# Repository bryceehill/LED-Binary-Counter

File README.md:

#Introduction

The Montana Tech Binary Counter is a project created by the Electrical Engineering Department.  All files to recreate it are available here.  Potential students can request a binary counter through this link:
https://www.mtech.edu/electrical-engineering/circuit-handout/index.html

To get started plug the binary counter into a computer via a USB cable.  In windows download putty.exe, find the port associated with the counter using "Device Manager" and open that serial port.
Getting started may need some direction.  Watch this video:
https://youtu.be/mpABhzl5tEQ

The current version of the binary counter is the ARM processor version.  You can find all connected files, firmware, designs within this repository.

# LED-Binary-Counter
Public Files for the LED Binary Counter.  Modify, Code, Change, on your own.

There are two versions.  The original one had a MSP430 G2553 as it's controller.  The new version uses an ATSAMD21E15B with added usb utility
Both chips have 10 LEDs that they control.

ARM - ATSAMD21E15B Documentation---------------------------------------------------------------------------

Pinout
PA00 - LED 0
PA01 - LED 1
PA02 - LED 2
PA03 - LED 3
PA04 - LED 4
PA05 - LED 5
PA06 - LED 6
PA07 - LED 7
PA08 - LED 8
PA09 - LED 9
PA16 - PushButton

MSP430 Documentation---------------------------------------------------------------------------------

This respository contains all of the files used to create the Montana Tech LED Bar Graph Counter
The bar graph counter is a piece of SWAG intended for potential students.
There are 10 LEDs controlled by an MSP430 G2553 Microcontroller (TI Look it up)

A PCB was created for use with the QFN-32 package of the G2553
Code was created using code composer studio in C programming language. All files are available
More instructions can be found for new users via the web page:
https://www.mtech.edu/electrical-engineering/circuit-handout/

Potential students can request a free complete system
Pinout of the MSP430 are the following
* 1.0 -
 * 1.1 - RX0  UART Receive
 * 1.2 - TX0  UART Transmit
 * 1.3 - SW1  Pushbutton
 * 1.4 -
 * 1.5 -
 * 1.6 -
 * 1.7 -
 * 2.0 - L8  LED 8
 * 2.1 - L9  LED 9
 * 2.2 -
 * 2.3 -
 * 2.4 -
 * 2.5 -
 * 2.6 -
 * 2.7 -
 * 3.0 - L0  LED 0
 * 3.1 - L1  LED 1
 * 3.2 - L2  LED 2
 * 3.3 - L3  LED 3
 * 3.4 - L4  LED 4
 * 3.5 - L5  LED 5
 * 3.6 - L6  LED 6
 * 3.7 - L7  LED 7

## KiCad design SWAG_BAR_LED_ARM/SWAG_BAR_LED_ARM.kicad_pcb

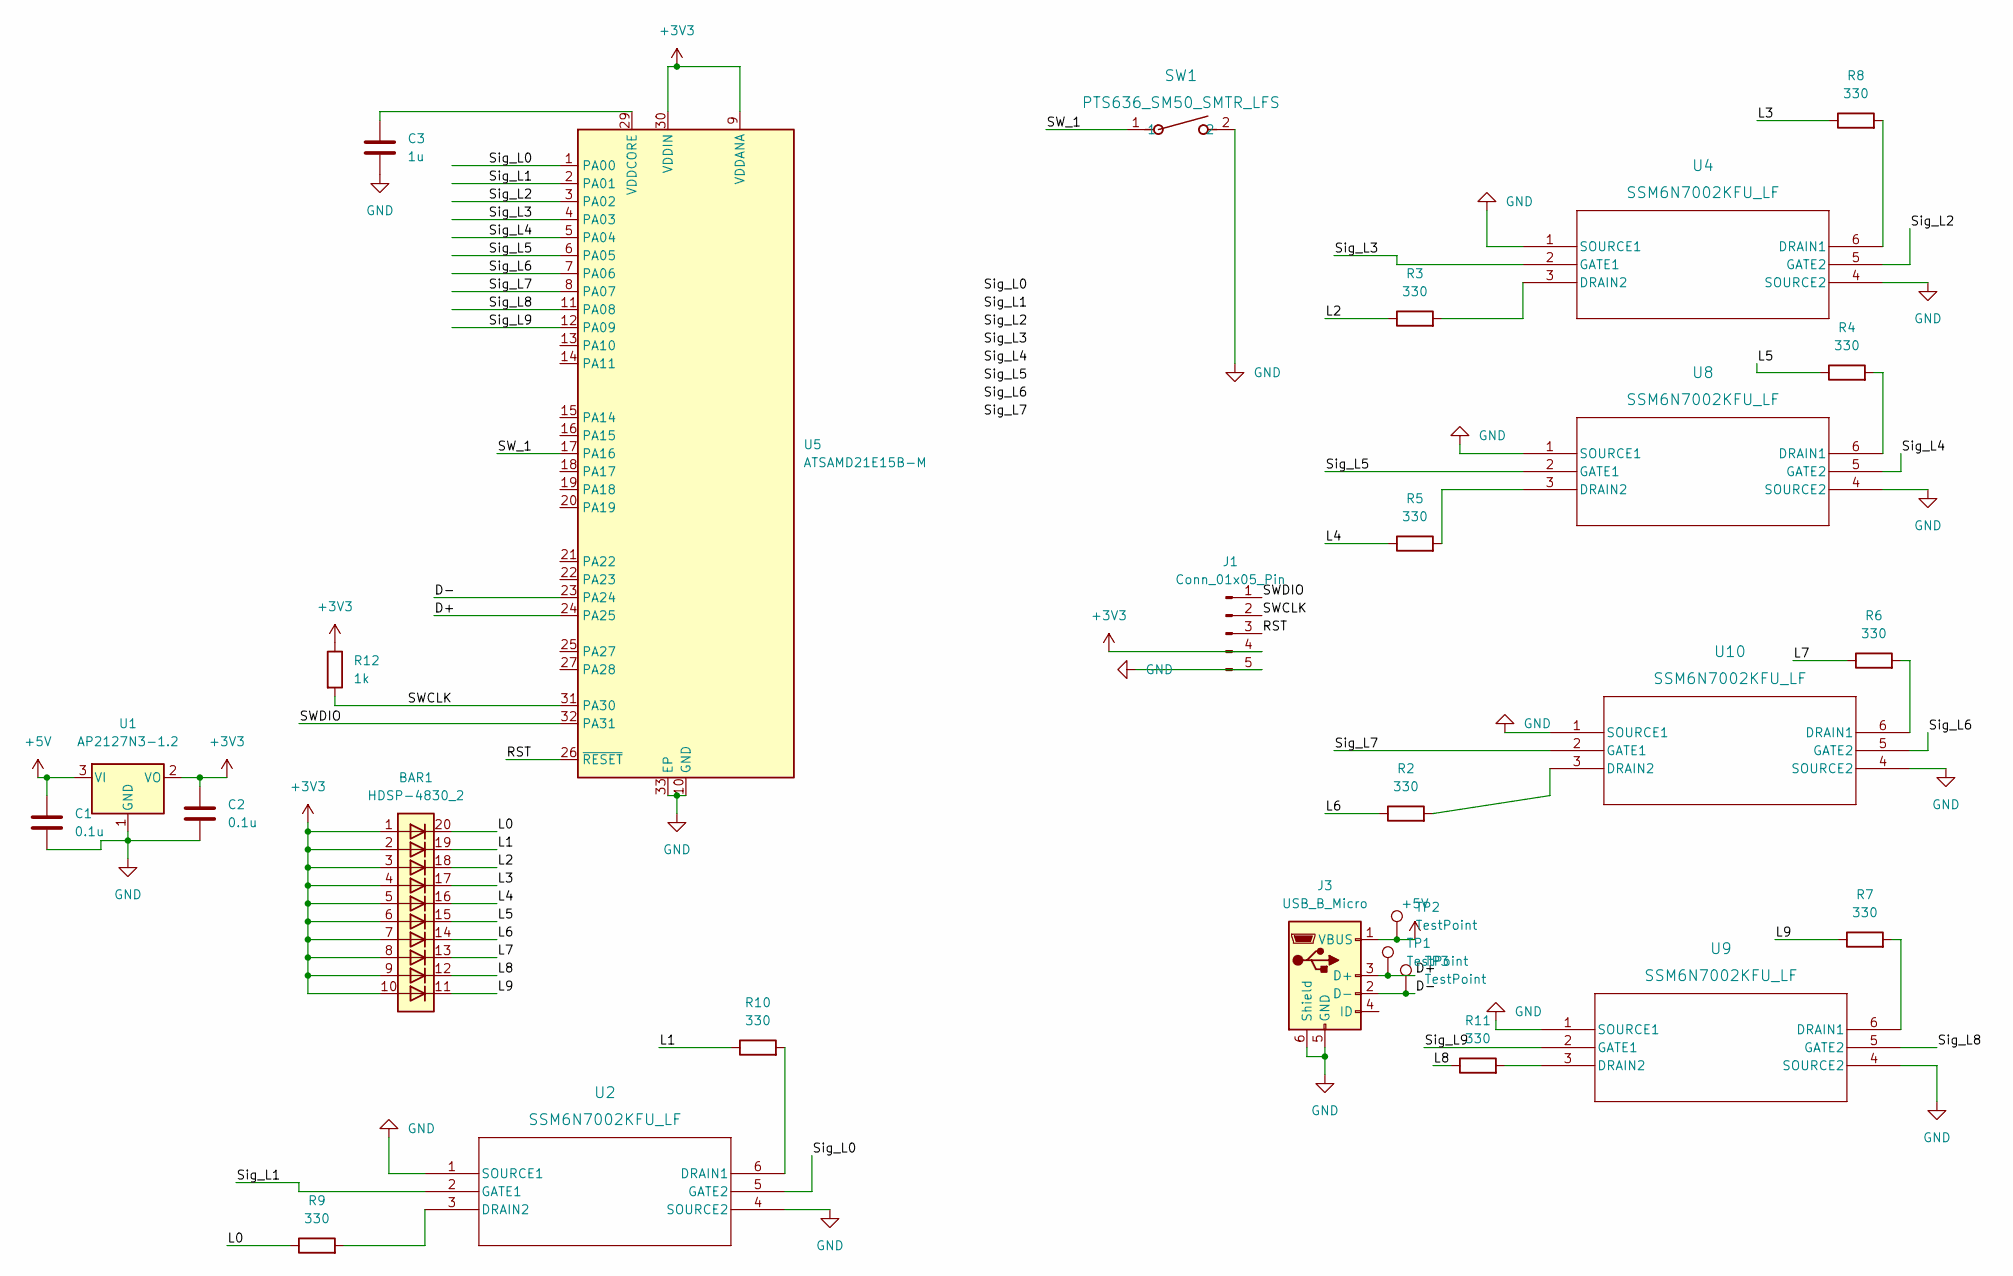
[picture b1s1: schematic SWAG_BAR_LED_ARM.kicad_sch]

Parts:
BAR1: HDSP-4830_2; HDSP-4830
C1, C2: 0.1u; C_0603_1608Metric
C3: 1u; C_0603_1608Metric
J1: Conn_01x05_Pin; PinHeader_1x05_P2.54mm_Vertical
J3: USB_B_Micro; USB_Micro-B_Wuerth_629105150521
R2, R3, R4, R5, R6, R7, R8, R9, R10, R11: 330; R_0603_1608Metric
R12: 1k; R_0603_1608Metric
SW1: PTS636_SM50_SMTR_LFS; SW_PTS636_SMT-G_5_CNK
TP1, TP2, TP3: TestPoint; TestPoint_Loop_D2.50mm_Drill1.0mm_LowProfile
U1: AP2127N3-1.2; TSOT-23
U2, U4, U8, U9, U10: SSM6N7002KFU_LF; SOT-363 US6_TOS
U5: ATSAMD21E15B-M; QFN-32-1EP_5x5mm_P0.5mm_EP3.6x3.6mm

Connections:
+3V3: BAR1.1 (A), BAR1.2 (A), BAR1.3 (A), BAR1.4 (A), BAR1.5 (A), BAR1.6 (A), BAR1.7 (A), BAR1.8 (A), BAR1.9 (A), BAR1.10 (A), C2.1, J1.4, R12.1, U1.2 (VO), U5.9 (VDDANA), U5.30 (VDDIN)
+5V: C1.1, J3.1 (VBUS), TP2.1, U1.3 (VI)
/D+: J3.3 (D+), TP1.1, U5.24 (PA25)
/D-: J3.2 (D-), TP3.1, U5.23 (PA24)
/L0: BAR1.20 (K), R9.1
/L1: BAR1.19 (K), R10.1
/L2: BAR1.18 (K), R3.1
/L3: BAR1.17 (K), R8.1
/L4: BAR1.16 (K), R5.1
/L5: BAR1.15 (K), R4.1
/L6: BAR1.14 (K), R2.1
/L7: BAR1.13 (K), R6.1
/L8: BAR1.12 (K), R11.1
/L9: BAR1.11 (K), R7.1
/RST: J1.3, U5.26 (~RESET)
/SWCLK: J1.2, R12.2, U5.31 (PA30)
/SWDIO: J1.1, U5.32 (PA31)
/SW_1: SW1.1, U5.17 (PA16)
/Sig_L0: U2.5 (GATE2), U5.1 (PA00)
/Sig_L1: U2.2 (GATE1), U5.2 (PA01)
/Sig_L2: U4.5 (GATE2), U5.3 (PA02)
/Sig_L3: U4.2 (GATE1), U5.4 (PA03)
/Sig_L4: U5.5 (PA04), U8.5 (GATE2)
/Sig_L5: U5.6 (PA05), U8.2 (GATE1)
/Sig_L6: U5.7 (PA06), U10.5 (GATE2)
/Sig_L7: U5.8 (PA07), U10.2 (GATE1)
/Sig_L8: U5.11 (PA08), U9.5 (GATE2)
/Sig_L9: U5.12 (PA09), U9.2 (GATE1)
GND: C1.2, C2.2, C3.2, J1.5, J3.5 (GND), J3.6 (Shield), SW1.2, U1.1 (GND), U2.1 (SOURCE1), U2.4 (SOURCE2), U4.1 (SOURCE1), U4.4 (SOURCE2), U5.10 (GND), U5.28 (GND), U5.33 (EP), U8.1 (SOURCE1), U8.4 (SOURCE2), U9.1 (SOURCE1), U9.4 (SOURCE2), U10.1 (SOURCE1), U10.4 (SOURCE2)
unnamed: R10.2, U2.6 (DRAIN1)
unnamed: R9.2, U2.3 (DRAIN2)
unnamed: R8.2, U4.6 (DRAIN1)
unnamed: R3.2, U4.3 (DRAIN2)
unnamed: C3.1, U5.29 (VDDCORE)
unnamed: R4.2, U8.6 (DRAIN1)
unnamed: R5.2, U8.3 (DRAIN2)
unnamed: R7.2, U9.6 (DRAIN1)
unnamed: R11.2, U9.3 (DRAIN2)
unnamed: R6.2, U10.6 (DRAIN1)
unnamed: R2.2, U10.3 (DRAIN2)

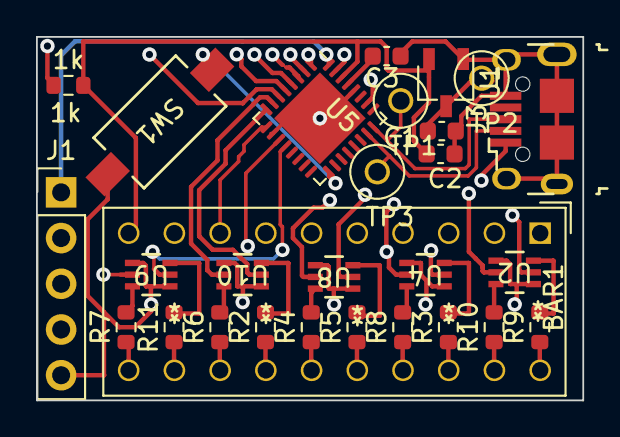
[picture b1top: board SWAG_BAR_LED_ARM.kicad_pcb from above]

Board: 4 copper layers, 30.4 x 20.2 mm, 28 parts (0 on the bottom side), 40 nets.

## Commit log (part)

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2023-12-11 KiCAD File upload
    Initial files for the SWAG Bar LED from KiCAD V7
2023-12-11 LED Bar Picture for reference
    Just a picture
2023-12-11 MSP430 CCS Code
    Code for the LED Bar Counter
2026-02-18 Update README with ATSAMD21E15B details
    Added documentation for ATSAMD21E15B version and its pinout.
